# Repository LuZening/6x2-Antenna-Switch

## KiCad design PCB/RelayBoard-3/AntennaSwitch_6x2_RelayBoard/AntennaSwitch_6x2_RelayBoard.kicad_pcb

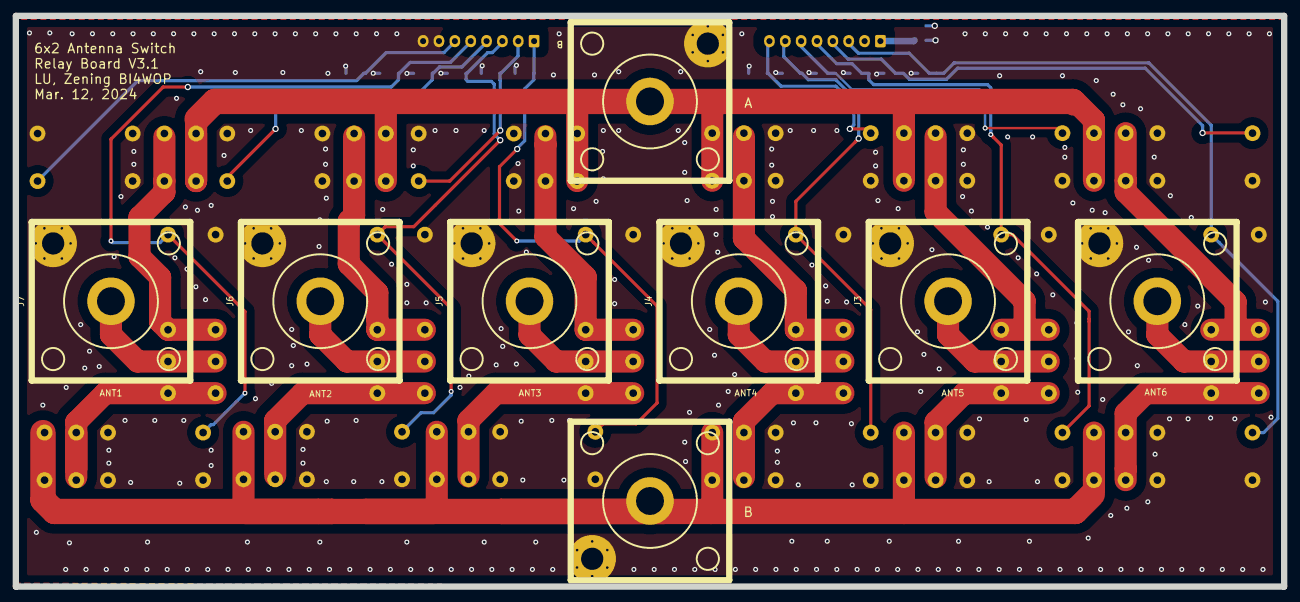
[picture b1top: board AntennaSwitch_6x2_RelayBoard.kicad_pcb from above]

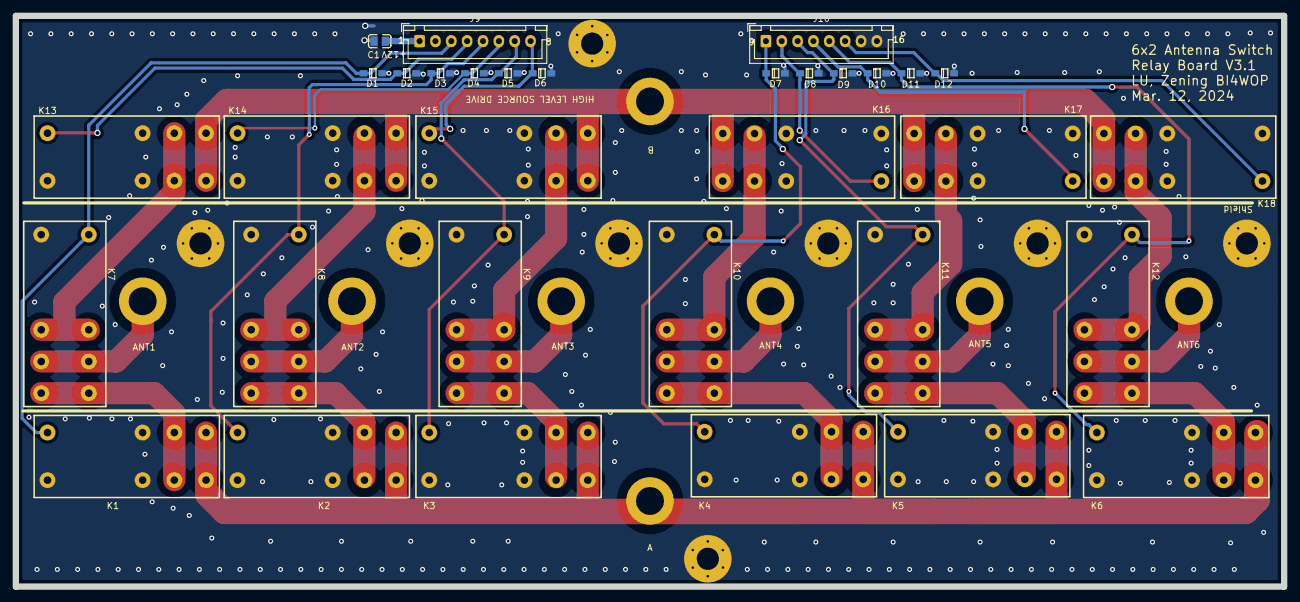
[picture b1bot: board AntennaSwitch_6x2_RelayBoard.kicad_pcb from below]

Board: 2 copper layers, 200.0 x 90.0 mm, 41 parts (33 on the bottom side), 34 nets.

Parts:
C1: 100uF; 0805_C
D1, D2, D3, D4, D5, D6, D7, D8, D9, D10, D11, D12: 1n4007; SOD-123
J1, J2, J3, J4, J5, J6, J7, J8: Conn_Coaxial; SL16_Screw_PCB
J9, J10: Conn_01x08; JST_XH_B8B-XH-A_1x08_P2.50mm_Vertical
K1, K2, K3, K4, K5, K6, K7, K8, K9, K10, K11, K12, K13, K14, K15, K16, K17, K18: G2RL-1-E

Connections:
+12V: C1.1, J9.1
/ANT1: J7.1, K12.3, K12.6
/ANT1_A: K6.3, K6.6, K12.4, K12.5
/ANT1_B: K12.2, K12.7, K18.3, K18.6
/ANT2: J6.1, K11.3, K11.6
/ANT2_A: K5.3, K5.6, K11.4, K11.5
/ANT2_B: K11.2, K11.7, K17.3, K17.6
/ANT3: J5.1, K10.3, K10.6
/ANT3_A: K4.3, K4.6, K10.4, K10.5
/ANT3_B: K10.2, K10.7, K16.3, K16.6
/ANT4: J4.1, K9.3, K9.6
/ANT4_A: K3.3, K3.6, K9.4, K9.5
/ANT4_B: K9.2, K9.7, K15.3, K15.6
/ANT5: J3.1, K8.3, K8.6
/ANT5_A: K2.3, K2.6, K8.4, K8.5
/ANT5_B: K8.2, K8.7, K14.3, K14.6
/ANT6: J2.1, K7.3, K7.6
/ANT6_A: K1.3, K1.6, K7.4, K7.5
/ANT6_B: K7.2, K7.7, K13.3, K13.6
/SEL2_1: D11.2, J10.5, K6.1, K12.1
/SEL2_2: D9.2, J10.3, K5.1, K11.1
/SEL2_3: D7.2, J10.1, K4.1, K10.1
A: J8.1, K13.4, K13.5, K14.4, K14.5, K15.4, K15.5, K16.4, K16.5, K17.4, K17.5, K18.4, K18.5
B: J1.1, K1.4, K1.5, K2.4, K2.5, K3.4, K3.5, K4.4, K4.5, K5.4, K5.5, K6.4, K6.5
GND: C1.2, D1.1, D2.1, D3.1, D4.1, D5.1, D6.1, D7.1, D8.1, D9.1, D10.1, D11.1, D12.1, J1.2, J2.2, J3.2, J4.2, J5.2, J6.2, J7.2, J8.2, J10.7, J10.8, K1.2, K1.7, K1.8, K2.2, K2.7, K2.8, K3.2, K3.7, K3.8, K4.2, K4.7, K4.8, K5.2, K5.7, K5.8, K6.2, K6.7, K6.8, K7.8, K8.8, K9.8, K10.8, K11.8, K12.8, K13.2, K13.7, K13.8, K14.2, K14.7, K14.8, K15.2, K15.7, K15.8, K16.2, K16.7, K16.8, K17.2, K17.7, K17.8, K18.2, K18.7, K18.8
unnamed: D1.2, J9.3, K1.1, K7.1
unnamed: D2.2, J9.4, K13.1
unnamed: D3.2, J9.5, K2.1, K8.1
unnamed: D4.2, J9.6, K14.1
unnamed: D5.2, J9.7, K3.1, K9.1
unnamed: D6.2, J9.8, K15.1
unnamed: D8.2, J10.2, K16.1
unnamed: D10.2, J10.4, K17.1
unnamed: D12.2, J10.6, K18.1

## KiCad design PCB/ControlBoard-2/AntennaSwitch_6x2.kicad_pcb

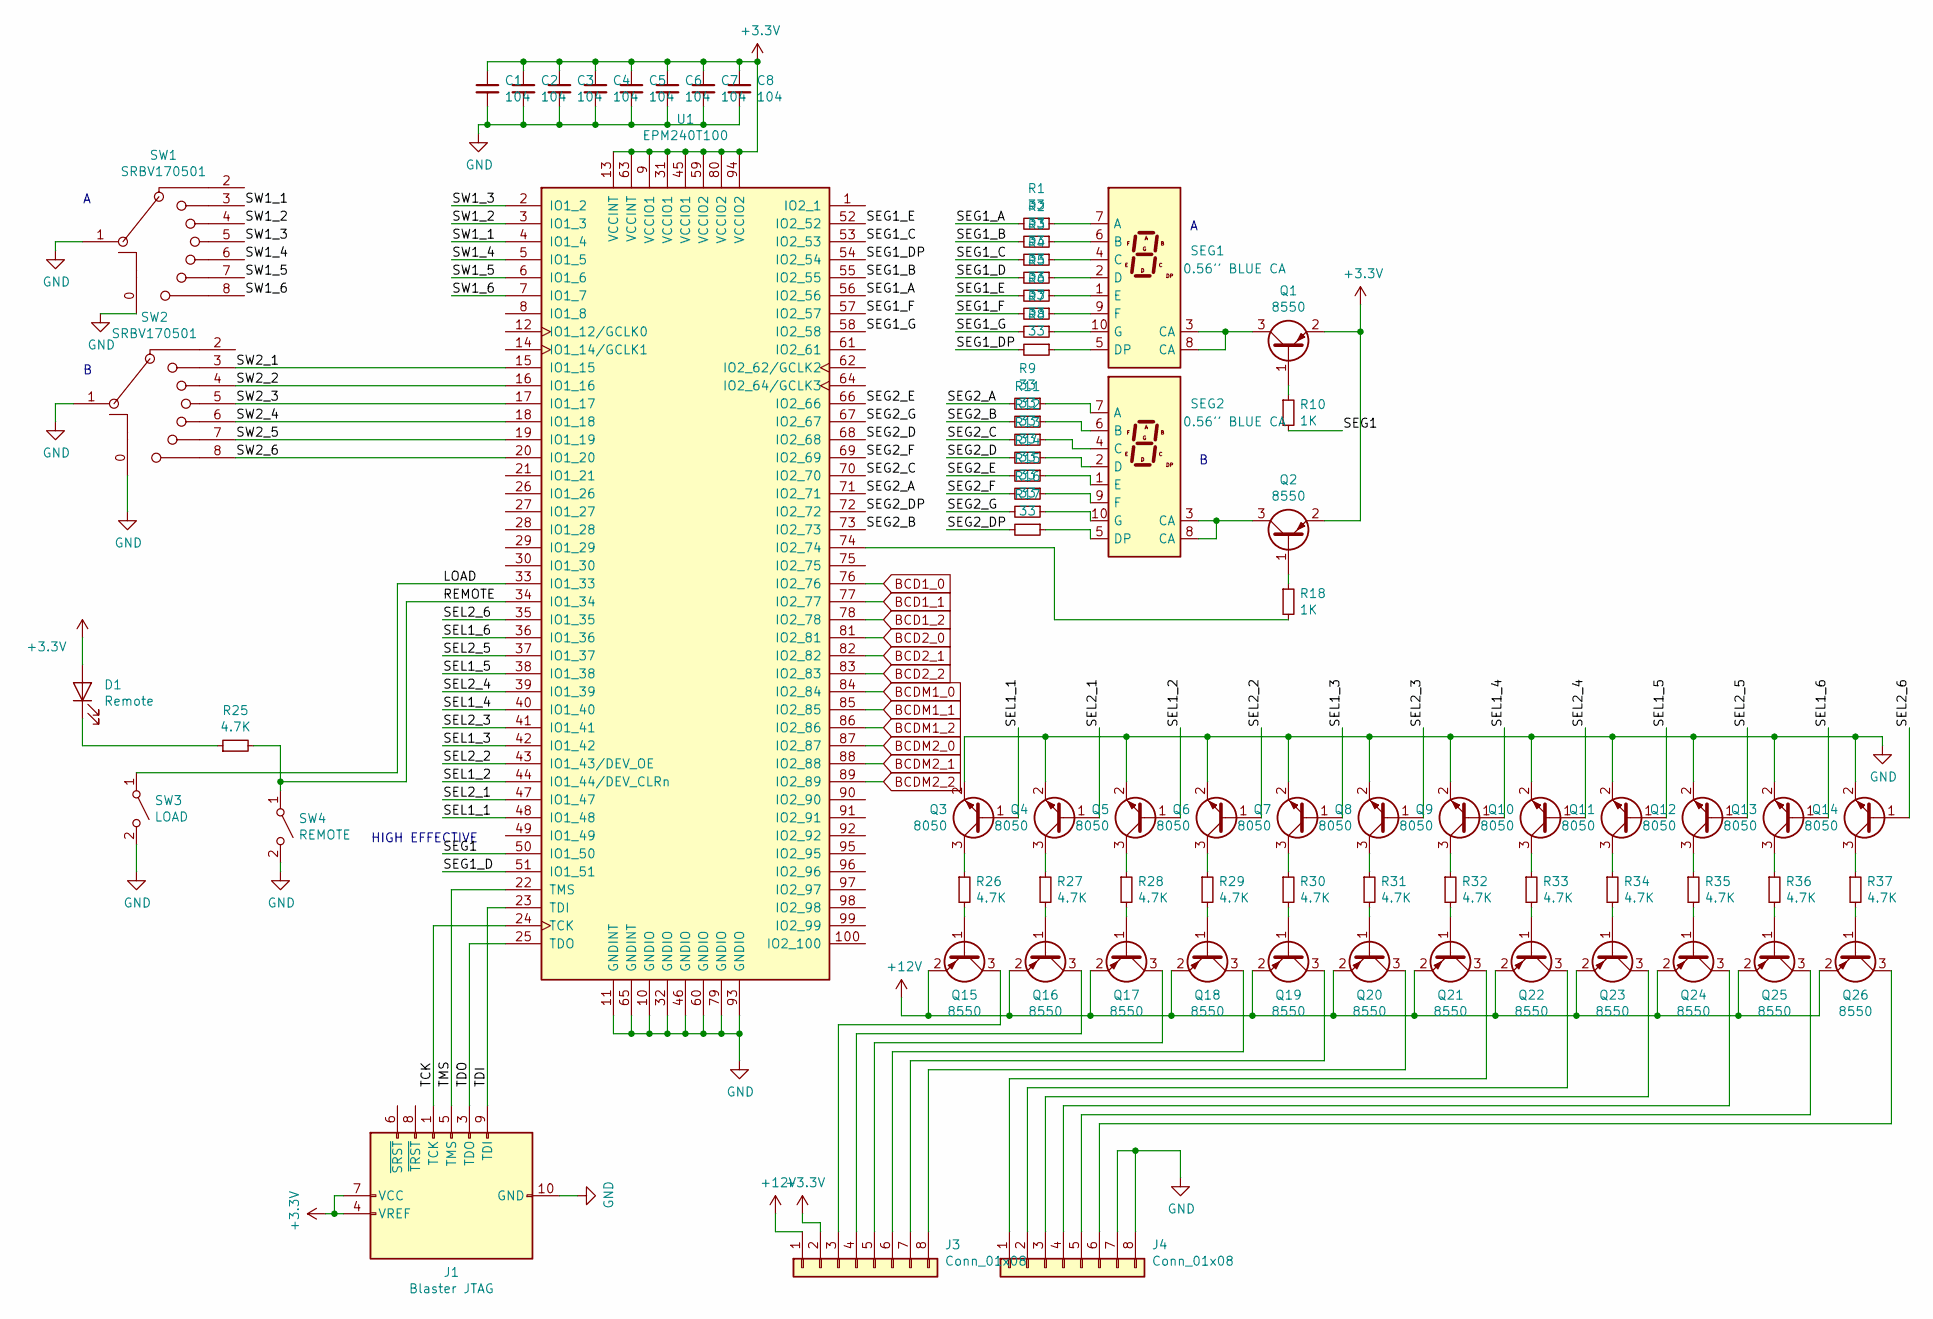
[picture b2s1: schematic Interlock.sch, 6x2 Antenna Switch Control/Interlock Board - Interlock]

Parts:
C1, C2, C3, C4, C5, C6, C7, C8: 104; 0603_C
D1: Remote; LED_D3.0mm
J1: Blaster JTAG; JTAG_10
J3, J4: Conn_01x08; JST_XH_B08B-XH-A_08x2.50mm_Straight
Q1, Q2, Q15, Q16, Q17, Q18, Q19, Q20, Q21, Q22, Q23, Q24, Q25, Q26: 8550; SOT-23(SOT-23-3)
Q3, Q4, Q5, Q6, Q7, Q8, Q9, Q10, Q11, Q12, Q13, Q14: 8050; SOT-23(SOT-23-3)
R1, R2, R3, R4, R5, R6, R7, R8, R9, R11, R12, R13, R14, R15, R16, R17: 33; 0603_R
R10, R18: 1K; 0603_R
R25, R26, R27, R28, R29, R30, R31, R32, R33, R34, R35, R36, R37: 4.7K; 0603_R
SEG1, SEG2: 0.56'' BLUE CA; 7SegmentLED_LTS6760_LTS6780
SW1, SW2: SRBV170501
SW3: LOAD; K8-7071
SW4: REMOTE; K8-7071
U1: EPM240T100; LQFP-100_14X14X05P

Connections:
+3V3: C1.1, C2.1, C3.1, C4.1, C5.1, C6.1, C7.1, C8.1, D1.2 (A), J1.4 (VREF), J1.7 (VCC), J3.2, Q1.2 (E), Q2.2 (E), U1.9 (VCCIO1), U1.13 (VCCINT), U1.31 (VCCIO1), U1.45 (VCCIO1), U1.59 (VCCIO2), U1.63 (VCCINT), U1.80 (VCCIO2), U1.94 (VCCIO2); also elsewhere on the board
+12V: J3.1, Q15.2 (E), Q16.2 (E), Q17.2 (E), Q18.2 (E), Q19.2 (E), Q20.2 (E), Q21.2 (E), Q22.2 (E), Q23.2 (E), Q24.2 (E), Q25.2 (E), Q26.2 (E); also elsewhere on the board
/Interlock/LOAD: SW3.1 (A), U1.33 (IO1_33)
/Interlock/REMOTE: R25.2, SW4.1 (A), U1.34 (IO1_34)
/Interlock/SEG1: R10.2, U1.50 (IO1_50)
/Interlock/SEG1_A: R1.2, U1.56 (IO2_56)
/Interlock/SEG1_B: R2.2, U1.55 (IO2_55)
/Interlock/SEG1_C: R3.2, U1.53 (IO2_53)
/Interlock/SEG1_D: R4.2, U1.51 (IO1_51)
/Interlock/SEG1_DP: R8.2, U1.54 (IO2_54)
/Interlock/SEG1_E: R5.2, U1.52 (IO2_52)
/Interlock/SEG1_F: R6.2, U1.57 (IO2_57)
/Interlock/SEG1_G: R7.2, U1.58 (IO2_58)
/Interlock/SEG2_A: R9.2, U1.71 (IO2_71)
/Interlock/SEG2_B: R11.2, U1.73 (IO2_73)
/Interlock/SEG2_C: R12.2, U1.70 (IO2_70)
/Interlock/SEG2_D: R13.2, U1.68 (IO2_68)
/Interlock/SEG2_DP: R17.2, U1.72 (IO2_72)
/Interlock/SEG2_E: R14.2, U1.66 (IO2_66)
/Interlock/SEG2_F: R15.2, U1.69 (IO2_69)
/Interlock/SEG2_G: R16.2, U1.67 (IO2_67)
/Interlock/SEL1_1: Q3.1 (B), U1.48 (IO1_48)
/Interlock/SEL1_2: Q5.1 (B), U1.44 (IO1_44/DEV_CLRn)
/Interlock/SEL1_3: Q7.1 (B), U1.42 (IO1_42)
/Interlock/SEL1_4: Q9.1 (B), U1.40 (IO1_40)
/Interlock/SEL1_5: Q11.1 (B), U1.38 (IO1_38)
/Interlock/SEL1_6: Q13.1 (B), U1.36 (IO1_36)
/Interlock/SEL2_1: Q4.1 (B), U1.47 (IO1_47)
/Interlock/SEL2_2: Q6.1 (B), U1.43 (IO1_43/DEV_OE)
/Interlock/SEL2_3: Q8.1 (B), U1.41 (IO1_41)
/Interlock/SEL2_4: Q10.1 (B), U1.39 (IO1_39)
/Interlock/SEL2_5: Q12.1 (B), U1.37 (IO1_37)
/Interlock/SEL2_6: Q14.1 (B), U1.35 (IO1_35)
/Interlock/SW1_1: SW1.3, U1.4 (IO1_4)
/Interlock/SW1_2: SW1.4, U1.3 (IO1_3)
/Interlock/SW1_3: SW1.5, U1.2 (IO1_2)
/Interlock/SW1_4: SW1.6, U1.5 (IO1_5)
/Interlock/SW1_5: SW1.7, U1.6 (IO1_6)
/Interlock/SW1_6: SW1.8, U1.7 (IO1_7)
/Interlock/SW2_1: SW2.3, U1.15 (IO1_15)
/Interlock/SW2_2: SW2.4, U1.16 (IO1_16)
/Interlock/SW2_3: SW2.5, U1.17 (IO1_17)
/Interlock/SW2_4: SW2.6, U1.18 (IO1_18)
/Interlock/SW2_5: SW2.7, U1.19 (IO1_19)
/Interlock/SW2_6: SW2.8, U1.20 (IO1_20)
/Interlock/TCK: J1.1 (TCK), U1.24 (TCK)
/Interlock/TDI: J1.9 (TDI), U1.23 (TDI)
/Interlock/TDO: J1.3 (TDO), U1.25 (TDO)
/Interlock/TMS: J1.5 (TMS), U1.22 (TMS)
BCD1_0: U1.76 (IO2_76); also elsewhere on the board
BCD1_1: U1.77 (IO2_77); also elsewhere on the board
BCD1_2: U1.78 (IO2_78); also elsewhere on the board
BCD2_0: U1.81 (IO2_81); also elsewhere on the board
BCD2_1: U1.82 (IO2_82); also elsewhere on the board
BCD2_2: U1.83 (IO2_83); also elsewhere on the board
BCDM1_0: U1.84 (IO2_84); also elsewhere on the board
BCDM1_1: U1.85 (IO2_85); also elsewhere on the board
BCDM1_2: U1.86 (IO2_86); also elsewhere on the board
BCDM2_0: U1.87 (IO2_87); also elsewhere on the board
BCDM2_1: U1.88 (IO2_88); also elsewhere on the board
BCDM2_2: U1.89 (IO2_89); also elsewhere on the board
unnamed: D1.1 (K), R25.1
unnamed: J3.3, Q15.3 (C)
unnamed: J3.4, Q16.3 (C)
unnamed: J3.5, Q17.3 (C)
unnamed: J3.6, Q18.3 (C)
unnamed: J3.7, Q19.3 (C)
unnamed: J3.8, Q20.3 (C)
unnamed: J4.1, Q21.3 (C)
unnamed: J4.2, Q22.3 (C)
unnamed: J4.3, Q23.3 (C)
unnamed: J4.4, Q24.3 (C)
unnamed: J4.5, Q25.3 (C)
unnamed: J4.6, Q26.3 (C)
unnamed: Q1.1 (B), R10.1
unnamed: Q1.3 (C), SEG1.3 (CA), SEG1.8 (CA)
unnamed: Q2.1 (B), R18.1
unnamed: Q2.3 (C), SEG2.3 (CA), SEG2.8 (CA)
unnamed: Q3.3 (C), R26.1
unnamed: Q4.3 (C), R27.1
unnamed: Q5.3 (C), R28.1
unnamed: Q6.3 (C), R29.1
unnamed: Q7.3 (C), R30.1
unnamed: Q8.3 (C), R31.1
unnamed: Q9.3 (C), R32.1
unnamed: Q10.3 (C), R33.1
unnamed: Q11.3 (C), R34.1
unnamed: Q12.3 (C), R35.1
unnamed: Q13.3 (C), R36.1
unnamed: Q14.3 (C), R37.1
unnamed: Q15.1 (B), R26.2
unnamed: Q16.1 (B), R27.2
unnamed: Q17.1 (B), R28.2
unnamed: Q18.1 (B), R29.2
unnamed: Q19.1 (B), R30.2
unnamed: Q20.1 (B), R31.2
unnamed: Q21.1 (B), R32.2
unnamed: Q22.1 (B), R33.2
unnamed: Q23.1 (B), R34.2
unnamed: Q24.1 (B), R35.2
unnamed: Q25.1 (B), R36.2
unnamed: Q26.1 (B), R37.2
unnamed: R1.1, SEG1.7 (A)
unnamed: R2.1, SEG1.6 (B)
unnamed: R3.1, SEG1.4 (C)
unnamed: R4.1, SEG1.2 (D)
unnamed: R5.1, SEG1.1 (E)
unnamed: R6.1, SEG1.9 (F)
unnamed: R7.1, SEG1.10 (G)
unnamed: R8.1, SEG1.5 (DP)
unnamed: R9.1, SEG2.7 (A)
unnamed: R11.1, SEG2.6 (B)
unnamed: R12.1, SEG2.4 (C)
unnamed: R13.1, SEG2.2 (D)
unnamed: R14.1, SEG2.1 (E)
unnamed: R15.1, SEG2.9 (F)
unnamed: R16.1, SEG2.10 (G)
unnamed: R17.1, SEG2.5 (DP)
unnamed: R18.2, U1.74 (IO2_74)
chasis: C1.2, C2.2, C3.2, C4.2, C5.2, C6.2, C7.2, C8.2, J1.2 (GND), J1.10 (GND), J4.7, J4.8, Q3.2 (E), Q4.2 (E), Q5.2 (E), Q6.2 (E), Q7.2 (E), Q8.2 (E), Q9.2 (E), Q10.2 (E), Q11.2 (E), Q12.2 (E), Q13.2 (E), Q14.2 (E), SW1.0 (Chasis), SW1.1, SW1.10, SW2.0 (Chasis), SW2.1, SW2.10, SW3.2 (B), SW4.2 (B), U1.10 (GNDIO), U1.11 (GNDINT), U1.32 (GNDIO), U1.46 (GNDIO), U1.60 (GNDIO), U1.65 (GNDINT), U1.79 (GNDIO), U1.93 (GNDIO); also elsewhere on the board

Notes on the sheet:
HIGH EFFECTIVE

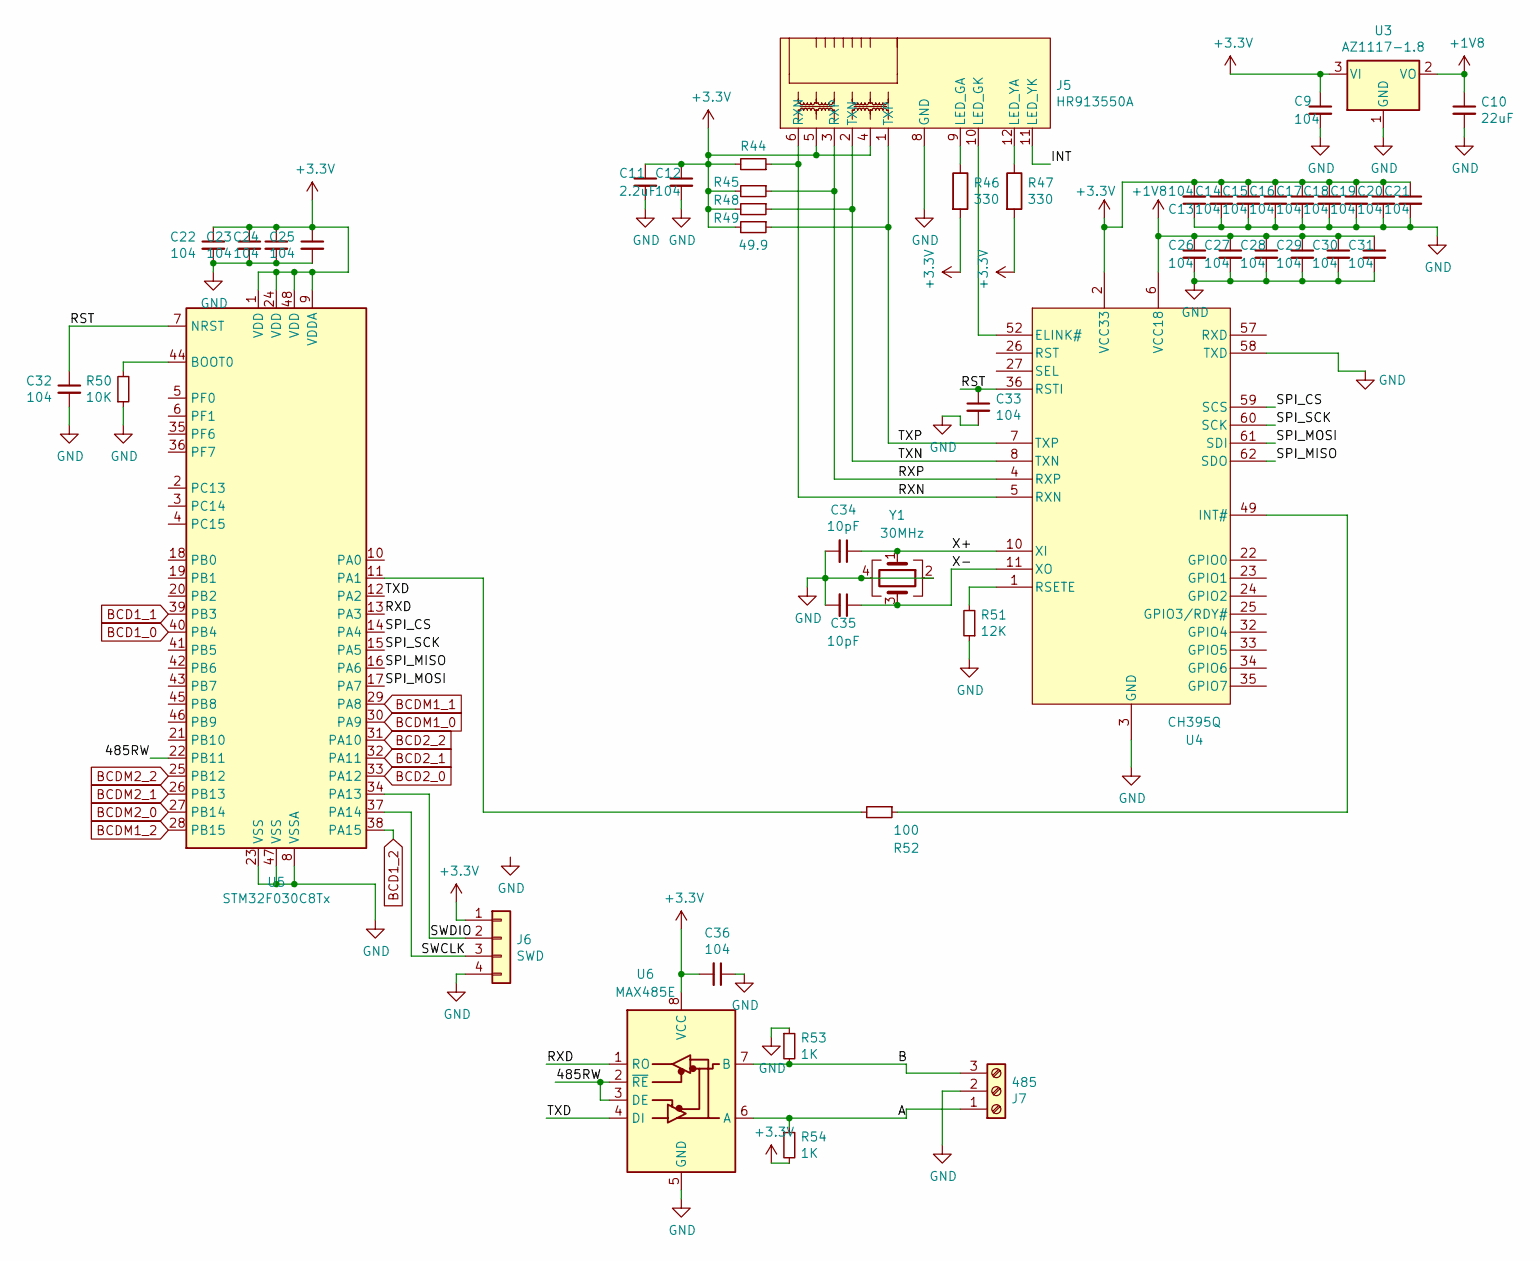
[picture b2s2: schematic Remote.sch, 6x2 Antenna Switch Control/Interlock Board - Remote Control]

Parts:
C9, C12, C13, C14, C15, C16, C17, C18, C19, C20, C21, C22, C23, C24, C25, C26, C27, C28, C29, C30, C31, C32, C33, C36: 104; 0603_C
C10: 22uF; 0805_C
C11: 2.2uF; 0805_C
C34, C35: 10pF; 0603_C
J5: HR913550A
J6: SWD; Pin_Header_Straight_1x04_Pitch2.54mm
J7: 485; PhoenixContact_MSTBA-G_03x5.08mm_Angled
R44, R45, R48, R49: 49.9; 0603_R
R46, R47: 330; 0603_R
R50: 10K; 0603_R
R51: 12K; 0603_R
R52: 100; 0603_R
R53, R54: 1K; 0603_R
U3: AZ1117-1.8; SOT-223
U4: CH395Q; LQFP-64_10X10X05P
U5: STM32F030C8Tx; LQFP-48_7X7X05P
U6: MAX485E; SOIC-8_W3.9mm
Y1: 30MHz; Crystal_SMD_3225-4pin_3.2x2.5mm

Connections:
+1V8: C10.1, C26.1, C27.1, C28.1, C29.1, C30.1, C31.1, U3.2 (VO), U4.6 (VCC18), U4.19 (VCC18), U4.28 (VCC18), U4.43 (VCC18), U4.54 (VCC18), U4.64 (VCC18)
+3V3: C9.1, C11.1, C12.1, C13.2, C14.1, C15.1, C16.1, C17.1, C18.1, C19.1, C20.1, C21.1, C22.1, C23.1, C24.1, C25.1, C36.2, J5.4, J5.5, J6.1, R44.2, R45.2, R46.2, R47.2, R48.2, R49.2, R54.2, U3.3 (VI), U4.2 (VCC33), U4.12 (VCC33), U4.17 (VCC33), U4.21 (VCC33), U4.29 (VCC33), U4.40 (VCC33), U4.42 (VCC33), U4.45 (VCC33), U4.63 (VCC33), U5.1 (VDD), U5.9 (VDDA), U5.24 (VDD), U5.48 (VDD), U6.8 (VCC); also elsewhere on the board
/Remote/485RW: U5.22 (PB11), U6.2 (~RE), U6.3 (DE)
/Remote/A: J7.1, R54.1, U6.6 (A)
/Remote/B: J7.3, R53.2, U6.7 (B)
/Remote/INT: J5.11 (LED_YK)
/Remote/RST: C32.1, C33.1, U4.36 (RSTI), U5.7 (NRST)
/Remote/RXD: U5.13 (PA3), U6.1 (RO)
/Remote/RXN: J5.6 (RXN), R44.1, U4.5 (RXN)
/Remote/RXP: J5.3 (RXP), R45.1, U4.4 (RXP)
/Remote/SPI_CS: U4.59 (SCS), U5.14 (PA4)
/Remote/SPI_MISO: U4.62 (SDO), U5.16 (PA6)
/Remote/SPI_MOSI: U4.61 (SDI), U5.17 (PA7)
/Remote/SPI_SCK: U4.60 (SCK), U5.15 (PA5)
/Remote/SWCLK: J6.3, U5.37 (PA14)
/Remote/SWDIO: J6.2, U5.34 (PA13)
/Remote/TXD: U5.12 (PA2), U6.4 (DI)
/Remote/TXN: J5.2 (TXN), R48.1, U4.8 (TXN)
/Remote/TXP: J5.1 (TXP), R49.1, U4.7 (TXP)
/Remote/X+: C34.1, U4.10 (XI), Y1.1
/Remote/X-: C35.1, U4.11 (XO), Y1.3
BCD1_0: U5.40 (PB4); also elsewhere on the board
BCD1_1: U5.39 (PB3); also elsewhere on the board
BCD1_2: U5.38 (PA15); also elsewhere on the board
BCD2_0: U5.33 (PA12); also elsewhere on the board
BCD2_1: U5.32 (PA11); also elsewhere on the board
BCD2_2: U5.31 (PA10); also elsewhere on the board
BCDM1_0: U5.30 (PA9); also elsewhere on the board
BCDM1_1: U5.29 (PA8); also elsewhere on the board
BCDM1_2: U5.28 (PB15); also elsewhere on the board
BCDM2_0: U5.27 (PB14); also elsewhere on the board
BCDM2_1: U5.26 (PB13); also elsewhere on the board
BCDM2_2: U5.25 (PB12); also elsewhere on the board
unnamed: J5.9 (LED_GA), R46.1
unnamed: J5.10 (LED_GK), U4.52 (ELINK#)
unnamed: J5.12 (LED_YA), R47.1
unnamed: R50.2, U5.44 (BOOT0)
unnamed: R51.2, U4.1 (RSETE)
unnamed: R52.1, U4.49 (INT#)
unnamed: R52.2, U5.11 (PA1)
chasis: C9.2, C10.2, C11.2, C12.2, C13.1, C14.2, C15.2, C16.2, C17.2, C18.2, C19.2, C20.2, C21.2, C22.2, C23.2, C24.2, C25.2, C26.2, C27.2, C28.2, C29.2, C30.2, C31.2, C32.2, C33.2, C34.2, C35.2, C36.1, J5.8 (GND), J6.4, J7.2, R50.1, R51.1, R53.1, U3.1 (GND), U4.3 (GND), U4.9 (GND), U4.13 (GND), U4.18 (GND), U4.20 (GND), U4.37 (GND), U4.41 (GND), U4.44 (GND), U4.48 (GND), U4.58 (TXD), U5.8 (VSSA), U5.23 (VSS), U5.47 (VSS), U6.5 (GND), Y1.2, Y1.4; also elsewhere on the board

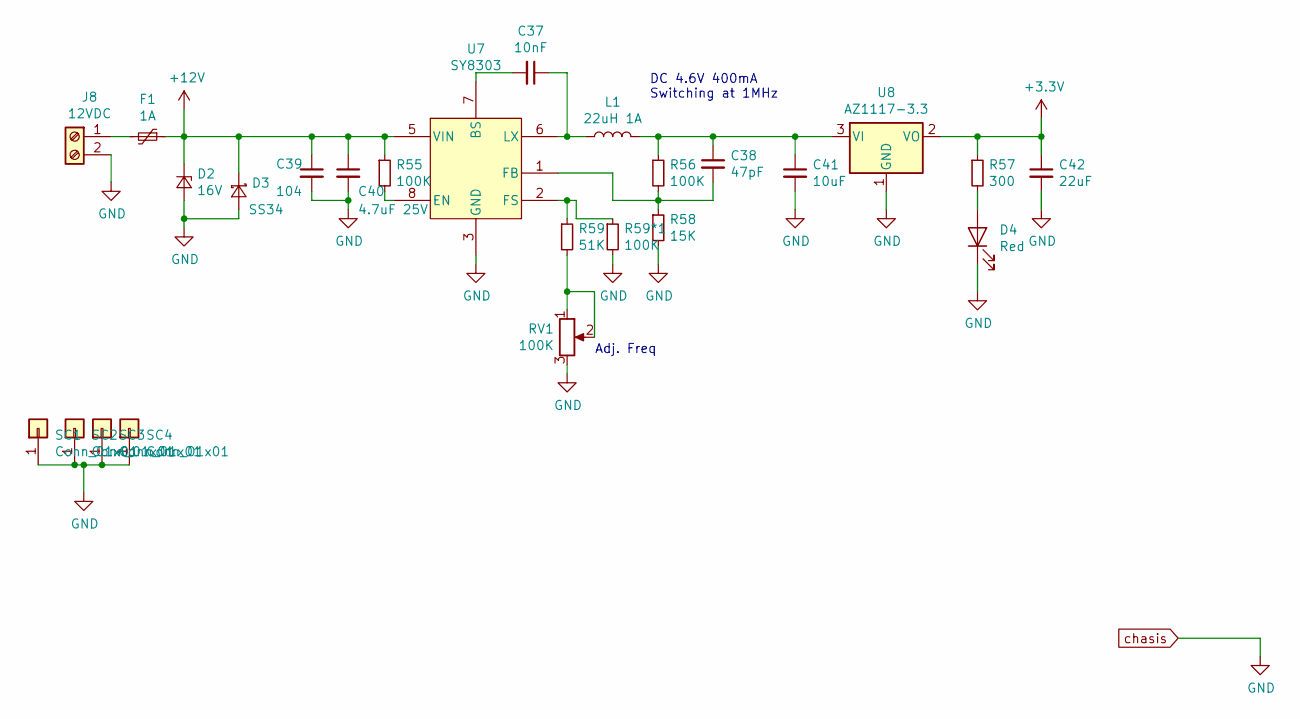
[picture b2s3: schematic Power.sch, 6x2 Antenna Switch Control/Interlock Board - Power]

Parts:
C37: 10nF; 0603_C
C38: 47pF; 0603_C
C39: 104; 0603_C
C40: 4.7uF 25V; 0805_C
C41: 10uF; 0805_C
C42: 22uF; 0805_C
D2: 16V; LL-34
D3: SS34; SMA(DO-214AC)_S3
D4: Red; LED_D3.0mm
F1: 1A; R_1812_HandSoldering
J8: 12VDC; PhoenixContact_MSTBA-G_02x5.08mm_Angled
L1: 22uH 1A; L_SMD4030_hand
R55, R56, R59*1: 100K; 0603_R
R57: 300; 0603_R
R58: 15K; 0603_R
R59: 51K; 0603_R
RV1: 100K; 3362P
SC1, SC2, SC3, SC4: Conn_01x01; M3_Screwhole
U7: SY8303; TSOT-23-8_HandSoldering
U8: AZ1117-3.3; SOT-223

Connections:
+3V3: C42.1, R57.1, U8.2 (VO); also elsewhere on the board
+12V: C39.1, C40.1, D2.1 (K), D3.2 (K), F1.1, R55.1, U7.5 (VIN); also elsewhere on the board
unnamed: C37.1, L1.1, U7.6 (LX)
unnamed: C37.2, U7.7 (BS)
unnamed: C38.1, C41.1, L1.2, R56.1, U8.3 (VI)
unnamed: C38.2, R56.2, R58.1, U7.1 (FB)
unnamed: D4.2 (A), R57.2
unnamed: F1.2, J8.1
unnamed: R55.2, U7.8 (EN)
unnamed: R59.1, R59*1.1, U7.2 (FS)
unnamed: R59.2, RV1.1, RV1.2
chasis: C39.2, C40.2, C41.2, C42.2, D2.2 (A), D3.1 (A), D4.1 (K), J8.2, R58.2, R59*1.2, RV1.3, SC1.1, SC2.1, SC3.1, SC4.1, U7.3 (GND), U7.4 (GND), U8.1 (GND); also elsewhere on the board

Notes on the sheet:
DC 4.6V 400mA Switching at 1MHz
Adj. Freq

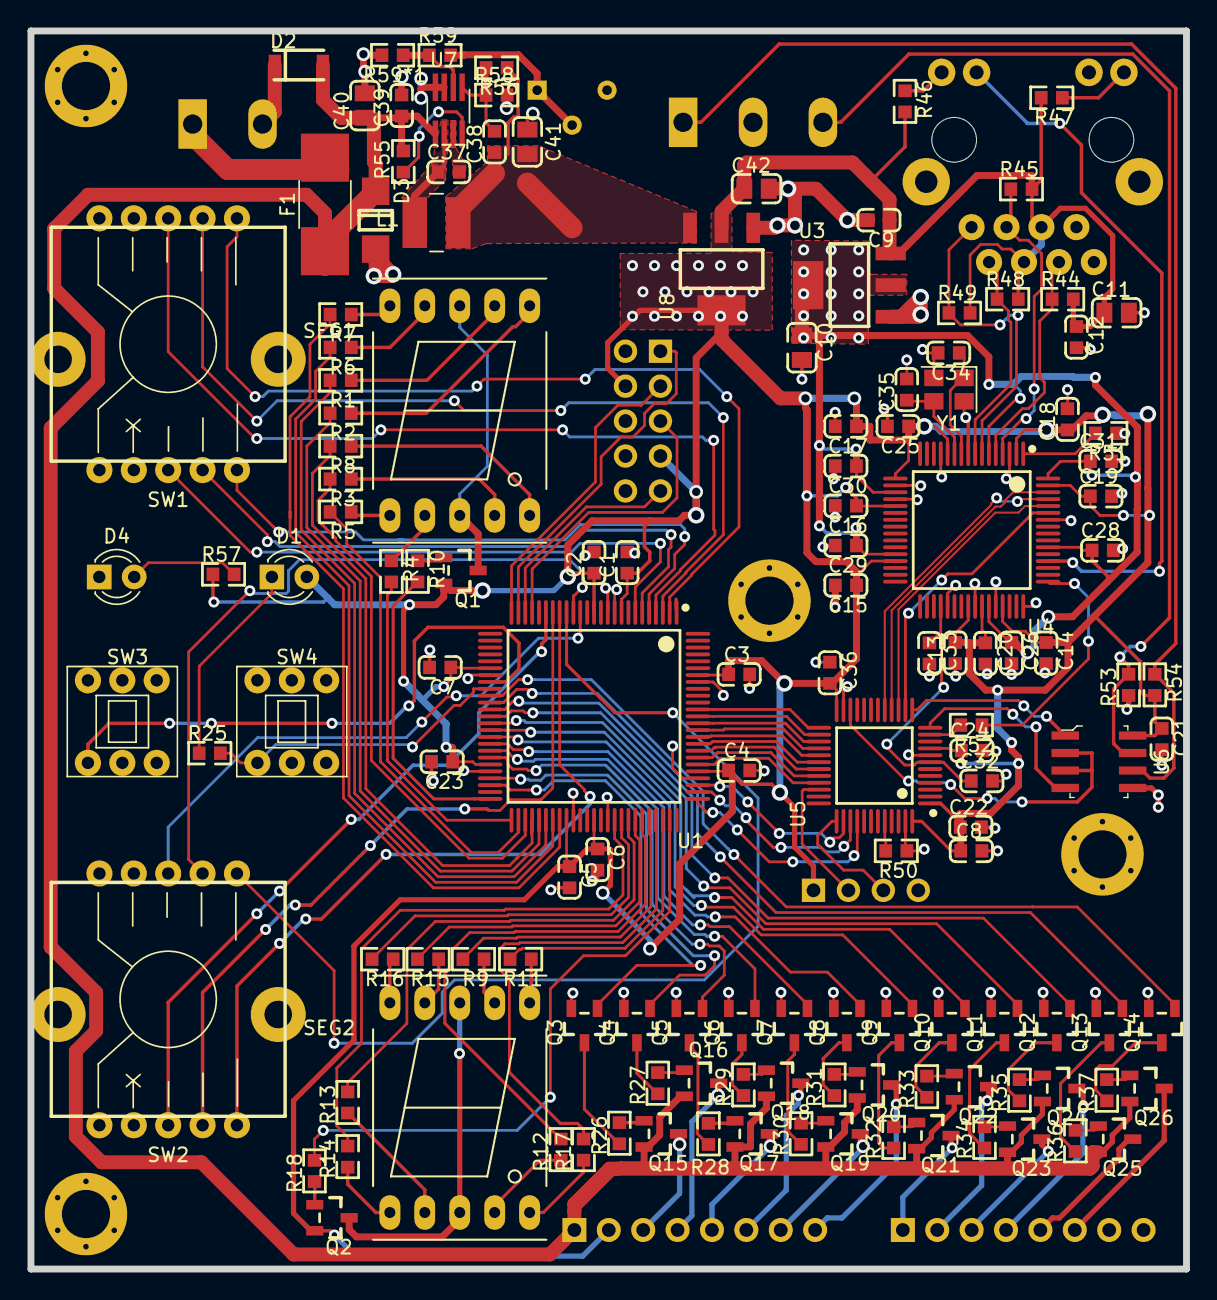
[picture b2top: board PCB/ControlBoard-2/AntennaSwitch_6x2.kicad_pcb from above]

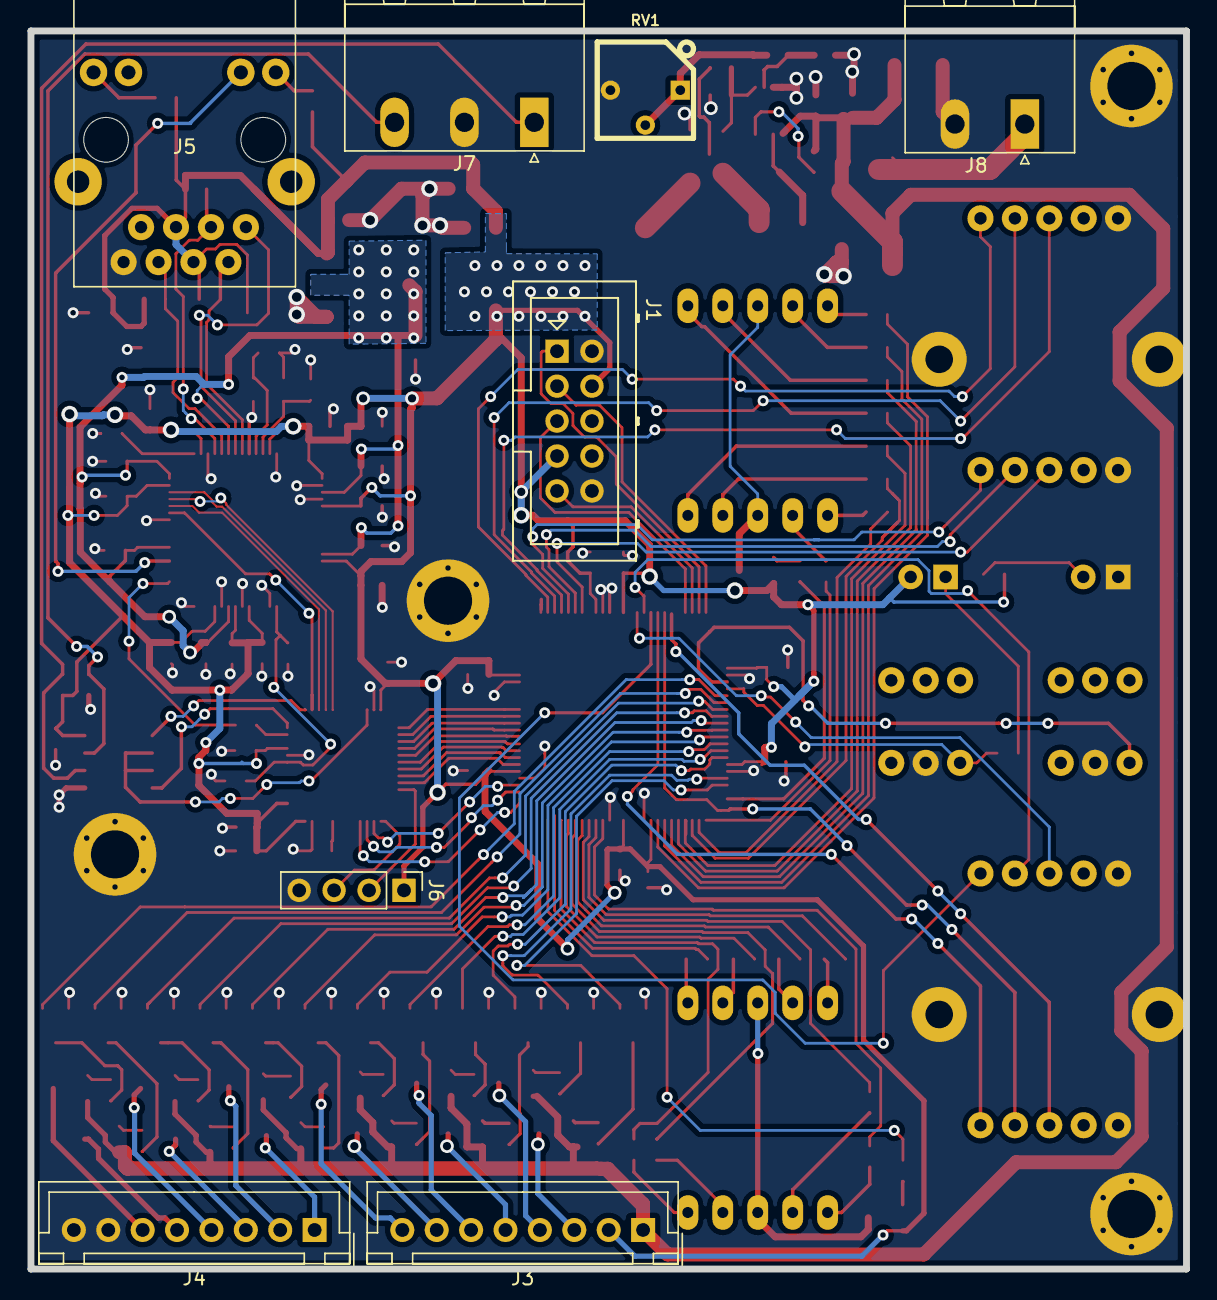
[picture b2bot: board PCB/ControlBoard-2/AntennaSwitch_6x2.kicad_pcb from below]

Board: 2 copper layers, 84.0 x 90.0 mm, 147 parts (8 on the bottom side), 155 nets.

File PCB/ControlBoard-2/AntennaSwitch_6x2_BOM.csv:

"Comment","Description","Designator","Footprint","LibRef","Pins","Quantity","PartNumber","url",
"2.2uF","desc","C11,","0805_C","libref","2","1","","",
"10pF","desc","C34,C35,","0603_C","libref","2","2","","",
"10nF","desc","C37,","0603_C","libref","2","1","","",
"47pF","desc","C38,","0603_C","libref","2","1","","",
"4.7uF 25V","desc","C40,","0805_C","libref","2","1","","",
"10uF","desc","C41,","0805_C","libref","2","1","","",
"22uF","desc","C42,C10,","0805_C","libref","2","2","","",
"104","desc","C43,C8,C6,C39,C36,C33,C32,C31,C30,C29,C28,C26,C25,C24,C23,C22,C21,C20,C19,C18,C17,C16,C15,C14,C13,C12,C9,C7,C5,C4,C3,C2,C1,","0603_C","libref","2","33","","",
"16V","desc","D2,","LL-34","libref","2","1","","",
"SS34","desc","D3,","SMA(DO-214AC)_S3","libref","2","1","","",
"1A","desc","F1,","R_1812_HandSoldering","libref","2","1","","",
"22uH 1A","desc","L1,","L_SMD4030_hand","libref","2","1","","",
"8050","desc","Q14,Q13,Q12,Q11,Q10,Q9,Q8,Q7,Q6,Q5,Q4,Q3,","SOT-23(SOT-23-3)","libref","3","12","","",
"8550","desc","Q26,Q25,Q24,Q23,Q22,Q21,Q20,Q19,Q18,Q17,Q16,Q15,Q2,Q1,","SOT-23(SOT-23-3)","libref","3","14","","",
"33","desc","R17,R16,R15,R8,R6,R4,R2,R1,R14,R13,R12,R11,R9,R7,R5,R3,","0603_R","libref","2","16","","",
"1K","desc","R19,R54,R10,R53,R18,","0603_R","libref","2","5","","",
"0","desc","R20,","1206_R","libref","2","1","","",
"4.7K","desc","R37,R36,R35,R34,R33,R32,R31,R30,R29,R28,R27,R26,R25,","0603_R","libref","2","13","","",
"330","desc","R47,R46,","0603_R","libref","2","2","","",
"49.9","desc","R49,R48,R45,R44,","0603_R","libref","2","4","","",
"10K","desc","R50,","0603_R","libref","2","1","","",
"12K","desc","R51,","0603_R","libref","2","1","","",
"100","desc","R52,","0603_R","libref","2","1","","",
"300","desc","R57,","0603_R","libref","2","1","","",
"15K","desc","R58,","0603_R","libref","2","1","","",
"51K","desc","R59,","0603_R","libref","2","1","","",
"100K","desc","R59*1,R56,R55,","0603_R","libref","2","3","","",
"47K","desc","R61,R60,R43,R42,R41,R40,R39,R38,R24,R23,R22,R21,","0603_R","libref","2","12","","",
"EPM240T100","desc","U1,","LQFP-100_14X14X05P","libref","100","1","","",
"AZ1117-1.8","desc","U3,","SOT-223","libref","4","1","","",
"CH395Q","desc","U4,","LQFP-64_10X10X05P","libref","64","1","","",
"STM32F030C8Tx","desc","U5,","LQFP-48_7X7X05P","libref","48","1","","",
"MAX485E","desc","U6,","SOIC-8_W3.9mm","libref","8","1","","",
"SY8303","desc","U7,","TSOT-23-8_HandSoldering","libref","8","1","","",
"AZ1117-3.3","desc","U8,","SOT-223","libref","4","1","","",
"74HC04","desc","U9,U2,","TSSOP-14","libref","14","2","","",
"30MHz","desc","Y1,","Crystal_SMD_3225-4pin_3.2x2.5mm","libref","4","1","","",
"Through Hole Items ",
"Remote","desc","D1,","LED_D3.0mm","libref","2","1","","",
"Red","desc","D4,","LED_D3.0mm","libref","2","1","","",
"Conn_01x01","desc","J2,","PINTST","libref","1","1","","",
"RST","desc","J9,","PINTST","libref","1","1","","",
"Conn_01x01","desc","SC4,SC3,SC2,SC1,","M3_Screwhole","libref","7","4","","",
"0.56'' BLUE CA","desc","SEG1,SEG2,","7SegmentLED_LTS6760_LTS6780","libref","10","2","","",
"SRBV170501","desc","SW2,SW1,","SRBV170501","libref","12","2","","",
"LOAD","desc","SW3,","K8-7071","libref","6","1","","",
"REMOTE","desc","SW4,","K8-7071","libref","6","1","","",
"Blaster JTAG","desc","J1,","JTAG_10","libref","10","1","","",
"Conn_01x08","desc","J4,J3,","JST_XH_B08B-XH-A_08x2.50mm_Straight","libref","8","2","","",
"HR913550A","desc","J5,","HR913550A","libref","16","1","","",
"SWD","desc","J6,","Pin_Header_Straight_1x04_Pitch2.54mm","libref","4","1","","",
"485","desc","J7,","PhoenixContact_MSTBA-G_03x5.08mm_Angled","libref","3","1","","",
"12VDC","desc","J8,","PhoenixContact_MSTBA-G_02x5.08mm_Angled","libref","2","1","","",
"100K","desc","RV1,","3362P","libref","3","1","","",
